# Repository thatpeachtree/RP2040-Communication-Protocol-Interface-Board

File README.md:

# RP2040-Communication-Protocol-Interface-Board
PCB interfacing RP2040 chip to I2C, PWM, UART, CAN, and SPI protocols.

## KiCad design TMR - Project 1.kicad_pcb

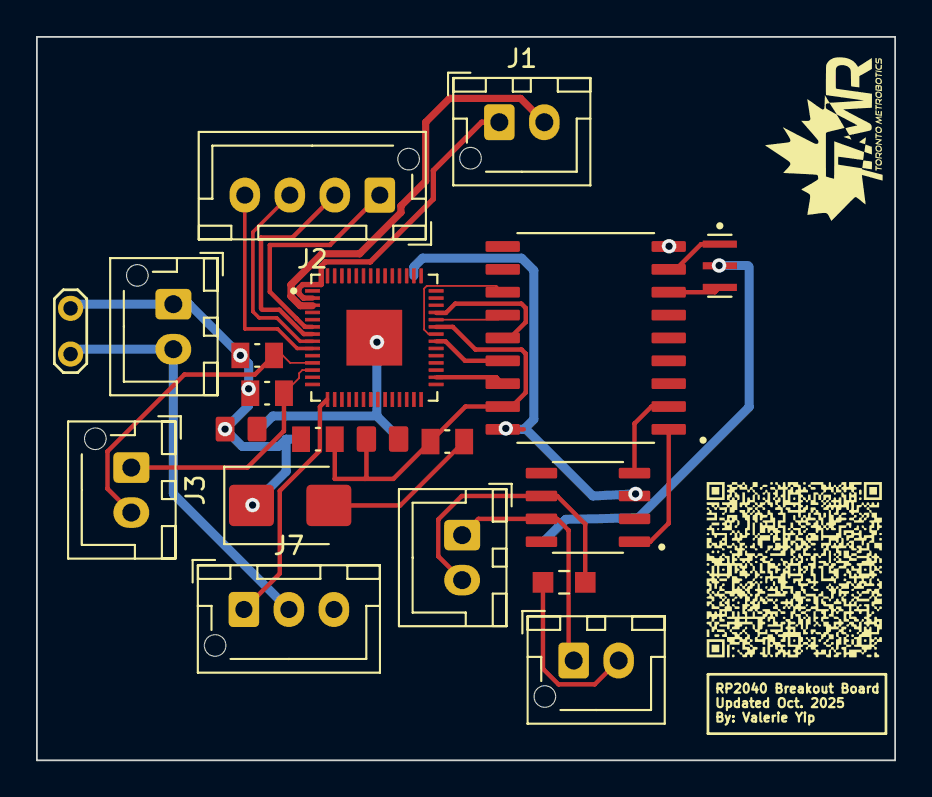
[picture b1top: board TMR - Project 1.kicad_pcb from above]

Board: 2 copper layers, 47.7 x 40.2 mm, 20 parts (0 on the bottom side), 25 nets.

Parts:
C1: 10u; CAPC2012X140N
C2: 100nF; CAPC2012X95N
D1: B230A-13-F; D_SMB
J1, J3, J4, J6: Conn_01x02_Pin; JST_XH_B2B-XH-AM_1x02_P2.50mm_Vertical
J2: Conn_01x04_Pin; JST_XH_B4B-XH-AM_1x04_P2.50mm_Vertical
J5: Conn_01x02_Pin; JST_XH_B2B-XH-A_1x02_P2.50mm_Vertical
J7: Conn_01x03_Pin; JST_XH_B3B-XH-AM_1x03_P2.50mm_Vertical
R1, R2: 1k; RESC2012X65N
R3: 120; RES_ERJP06D1200V
R4, R5: 2k; RESC2012X65N
TP1: TestPoint_2Pole; TestPoint_2Pads_Pitch2.54mm_Drill0.8mm
U1: RP2040; QFN40P700X700X90-57N
U2: MCP2515-I_SO; SOIC127P1030X265-18N
U3: TJA1050T; SOIC127P600X175-8N
Y1: 8MHz crystal res; OSC_CSTNE8M00G550000R0

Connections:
+5V: C2.1, D1.1 (K), J6.1, R2.1, R4.1, R5.1, TP1.1, U1.44 (VREG_VIN), U2.18 (VDD), U3.3 (VCC)
CANL: J5.2, R3.2, U3.6 (CANL)
CS: U1.30 (GPIO19), U2.16 (~CS)
CSn: J2.2, U1.7 (GPIO5)
Clk: J2.3, U1.8 (GPIO6)
GND: C1.2, C2.2, J6.2, J7.2, TP1.2, U1.57 (GND), U2.9 (VSS), U3.2 (GND), U3.8 (S), Y1.2
INT: U1.36 (GPIO24), U2.12 (~INT)
MISO: U1.35 (GPIO23), U2.15 (SO)
unnamed: D1.2 (A), R1.2
unnamed: J4.1, J5.1, U3.7 (CANH)
unnamed: J4.2, R3.1
OSC1: U2.8 (OSC1), Y1.1
OSC2: U2.7 (OSC2), Y1.3
PWM_OUT: J7.1, U1.15 (GPIO12)
RESET: C1.1, R1.1, R2.2, U1.37 (GPIO25), U2.17 (~RESET)
RX: J2.1, U1.6 (GPIO4)
RX1: J1.2, U1.3 (GPIO1)
RX2: U2.2 (RXCAN), U3.4 (RXD)
SCK: U1.38 (GPIO26/ADC0), U2.13 (SCK)
SCL: J3.2, R4.2, U1.11 (GPIO8)
SDA: J3.1, R5.2, U1.12 (GPIO9)
SI: U1.39 (GPIO27/ADC1), U2.14 (SI)
TX: J2.4, U1.9 (GPIO7)
TX1: J1.1, U1.2 (GPIO0)
TX2: U2.1 (TXCAN), U3.1 (TXD)
